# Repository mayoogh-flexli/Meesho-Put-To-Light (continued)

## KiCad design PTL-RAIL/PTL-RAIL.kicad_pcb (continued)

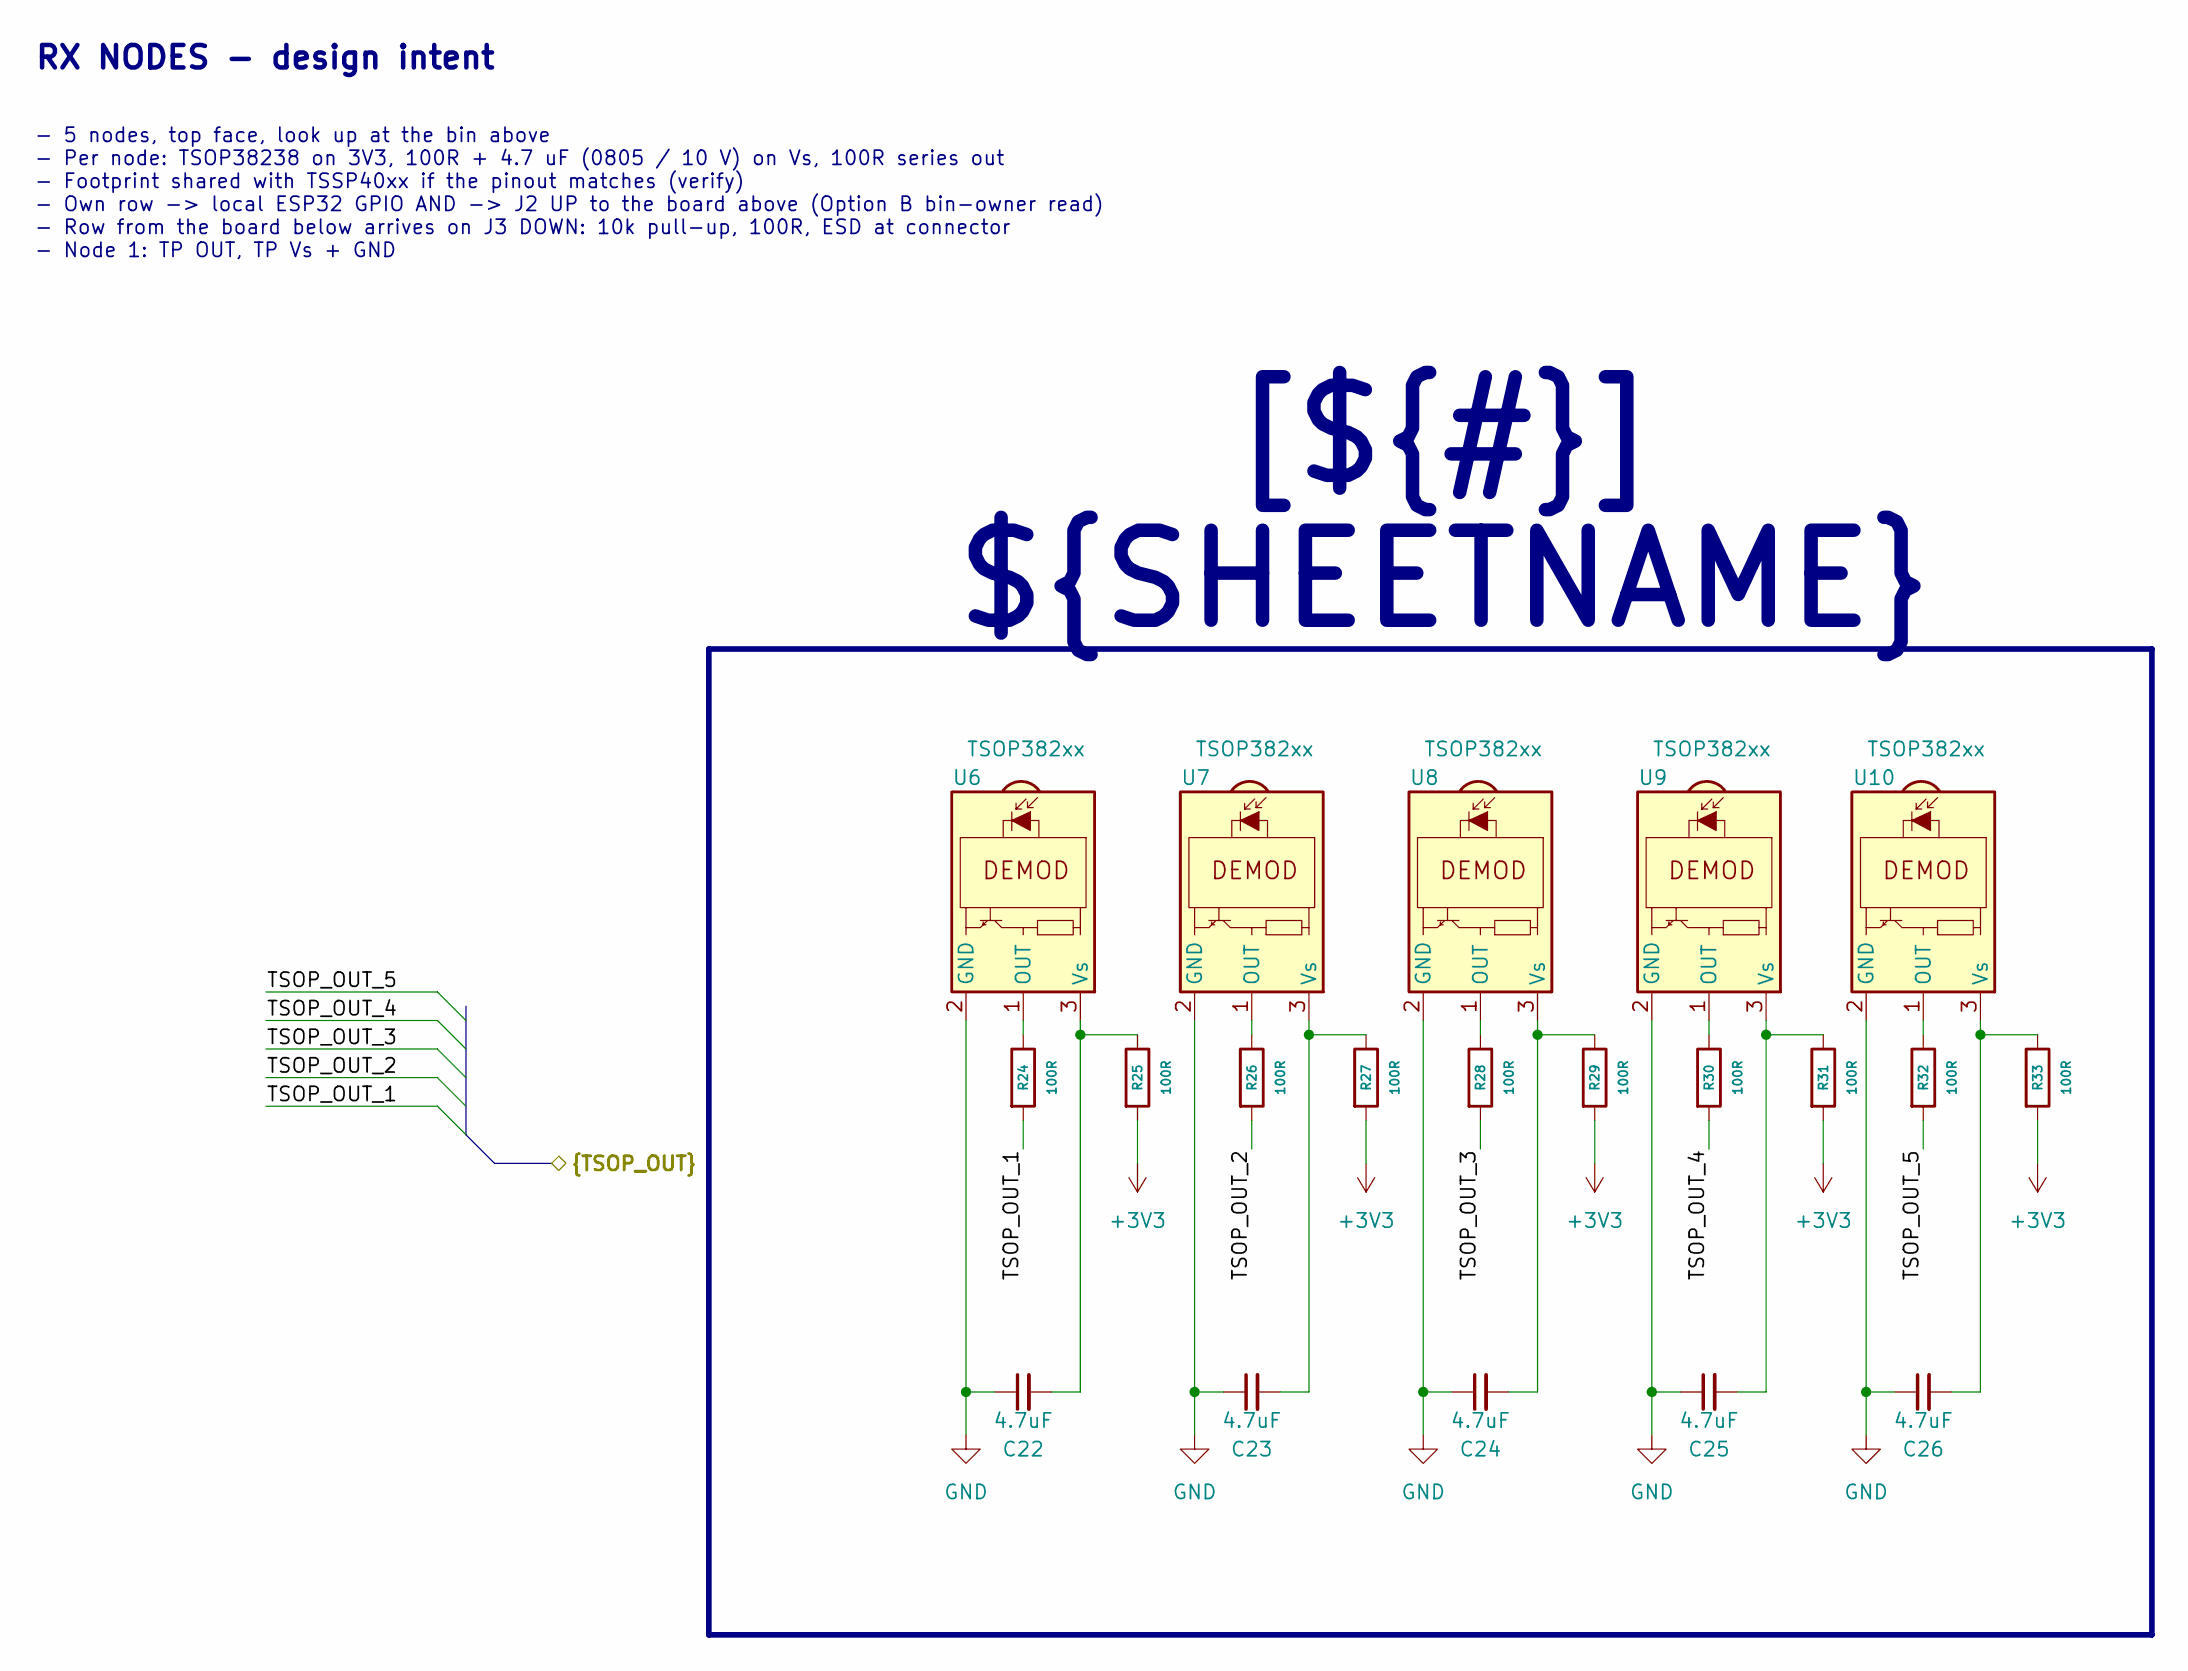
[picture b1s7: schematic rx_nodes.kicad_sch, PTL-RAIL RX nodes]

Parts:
C22, C23, C24, C25, C26: 4.7uF; C_0805_2012Metric
R24, R25, R26, R27, R28, R29, R30, R31, R32, R33: 100R; R_0805_2012Metric
U6, U7, U8, U9, U10: TSOP382xx; Vishay_MINICAST-3Pin

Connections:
+3V3: R25.2, R27.2, R29.2, R31.2, R33.2; also elsewhere on the board
/ESP32/TSOP_OUT_1: R24.2; also elsewhere on the board
/ESP32/TSOP_OUT_2: R26.2; also elsewhere on the board
/ESP32/TSOP_OUT_3: R28.2; also elsewhere on the board
/ESP32/TSOP_OUT_4: R30.2; also elsewhere on the board
/ESP32/TSOP_OUT_5: R32.2; also elsewhere on the board
GND: C22.1, C23.1, C24.1, C25.1, C26.1, U6.2 (GND), U7.2 (GND), U8.2 (GND), U9.2 (GND), U10.2 (GND); also elsewhere on the board
unnamed: R24.1, U6.1 (OUT)
unnamed: C22.2, R25.1, U6.3 (Vs)
unnamed: R26.1, U7.1 (OUT)
unnamed: C23.2, R27.1, U7.3 (Vs)
unnamed: R28.1, U8.1 (OUT)
unnamed: C24.2, R29.1, U8.3 (Vs)
unnamed: R30.1, U9.1 (OUT)
unnamed: C25.2, R31.1, U9.3 (Vs)
unnamed: R32.1, U10.1 (OUT)
unnamed: C26.2, R33.1, U10.3 (Vs)

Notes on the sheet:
- 5 nodes, top face, look up at the bin above - Per node: TSOP38238 on 3V3, 100R + 4.7 uF (0805 / 10 V) on Vs, 100R series out - Footprint shared with TSSP40xx if the pinout matches (verify) - Own row -> local ESP32 GPIO AND -> J2 UP to the board above (Option B bin-owner read) - Row from the board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
RX NODES - design intent
[${#}] ${SHEETNAME}

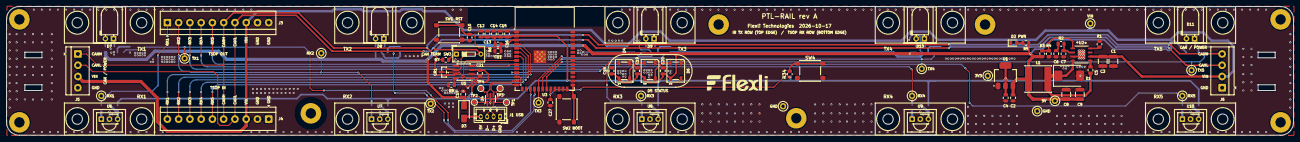
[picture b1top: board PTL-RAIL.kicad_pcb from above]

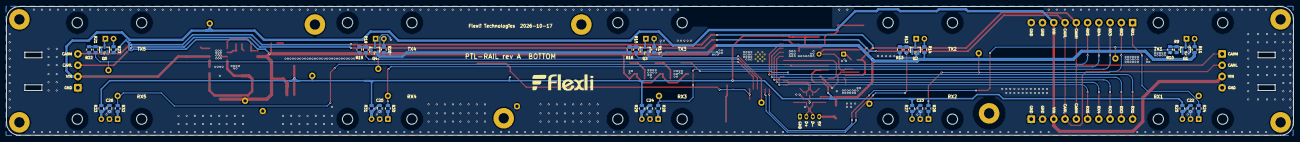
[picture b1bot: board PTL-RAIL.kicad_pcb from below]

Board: 2 copper layers, 400.0 x 40.0 mm, 145 parts (35 on the bottom side), 68 nets.

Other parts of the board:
H1, H2, H3, H4, H25, H26, H27, H28: MountingHole_M3; MountingHole_3.2mm_M3_Pad
H5, H6, H7, H8, H9, H10, H11, H12, H13, H14, H15, H16, H17, H18, H19, H20, H21, H22, H23, H24: MountingHole_3.2mm_M3
